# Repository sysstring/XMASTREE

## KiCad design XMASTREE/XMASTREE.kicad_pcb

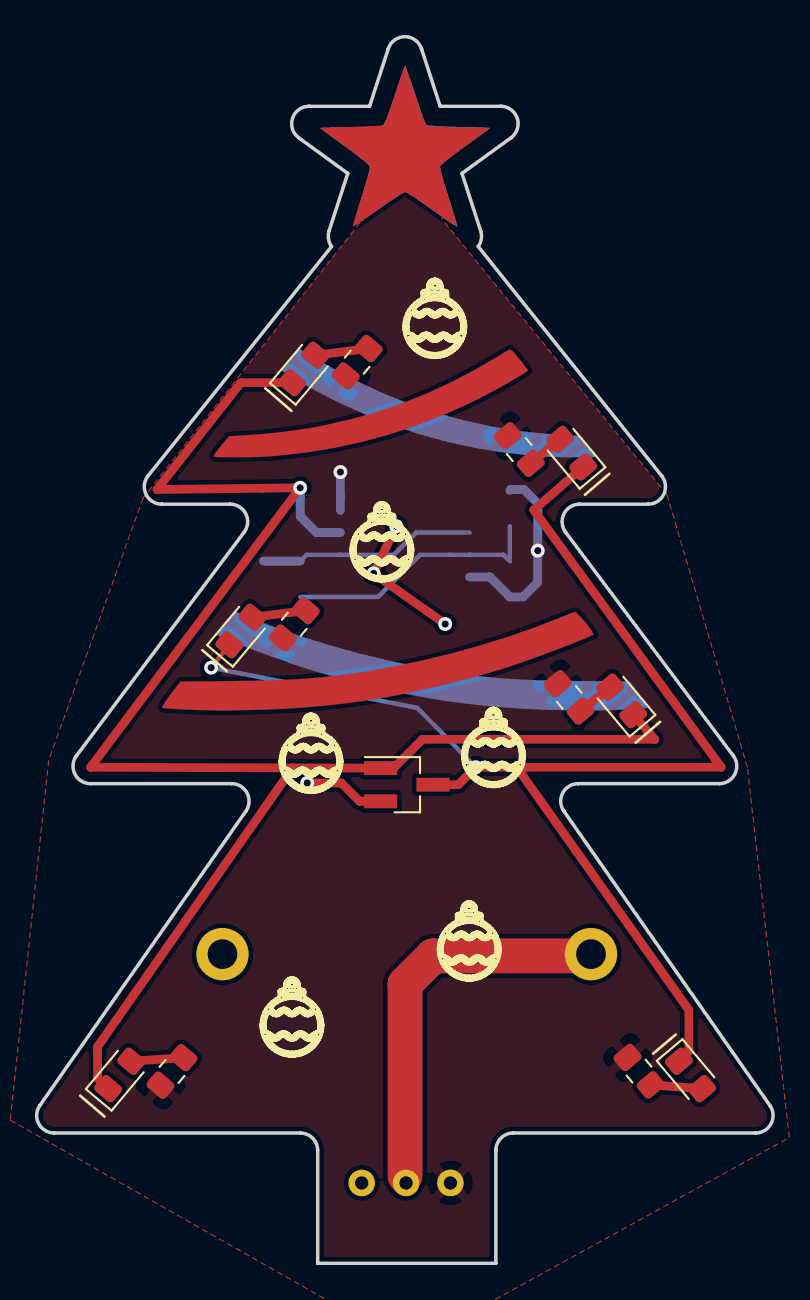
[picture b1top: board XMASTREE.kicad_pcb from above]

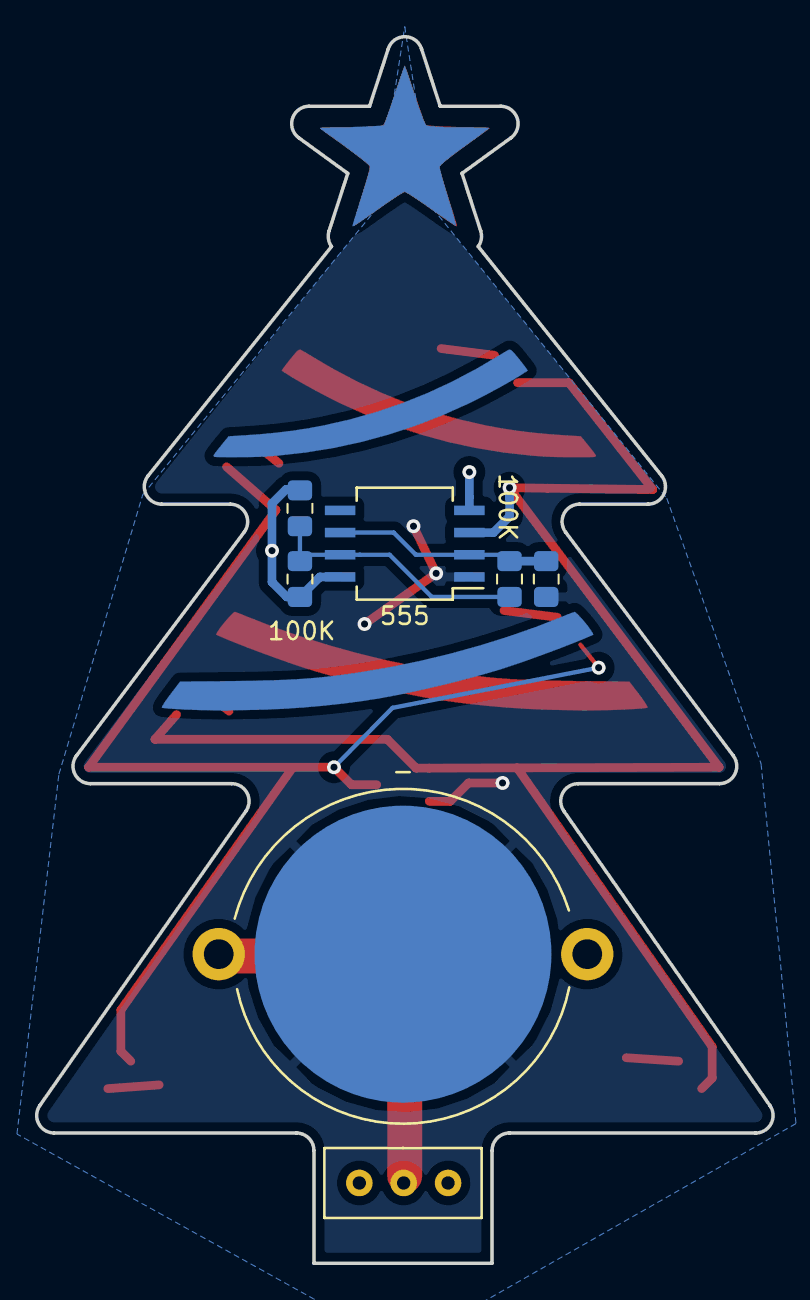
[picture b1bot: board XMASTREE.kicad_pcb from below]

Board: 2 copper layers, 42.2 x 70.2 mm, 22 parts (8 on the bottom side), 13 nets.

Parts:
100K: 100k; R_0805_2012Metric_Pad1.15x1.40mm_HandSolder
100K#2, 100K#3: 100K; R_0805_2012Metric_Pad1.15x1.40mm_HandSolder
555: TLC555; SO-8_5.3x6.2mm_P1.27mm
BT1: C2032
C1: 10u; C_0805_2012Metric_Pad1.15x1.40mm_HandSolder
D1, D2, D3, D4, D5, D6: LED; LED_0805_2012Metric_Pad1.15x1.40mm_HandSolder
Q1: Q_NMOS_GSD; SOT-23_Handsoldering
R1, R2, R4, R5, R6: 1K; R_0805_2012Metric_Pad1.15x1.40mm_HandSolder
SW1: SW_SPDT; 2.54mm_4x9mm_SPDT
TP1: Front side decoratoins; Decorations
TP2: Back side decorations; Decorations
e: 1K; R_0805_2012Metric_Pad1.15x1.40mm_HandSolder

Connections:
+BATT: 100K.1, 100K#2.2, 555.4, 555.8, R1.1, R2.1, R4.1, R5.1, R6.1, SW1.1, e.1
/BTN_COM: BT1.1, SW1.2
/INVERTED: D4.1, D5.1, D6.1, Q1.3
/OUTPUT: 555.3, D1.1, D2.1, D3.1, Q1.1
GND: 555.1, BT1.2, C1.2, Q1.2
unnamed: 100K#3.1, 555.2, 555.6, C1.1
unnamed: D1.2, R1.2
unnamed: D2.2, R2.2
unnamed: D3.2, e.2
unnamed: D4.2, R4.2
unnamed: D5.2, R5.2
unnamed: D6.2, R6.2
unnamed: 100K.2, 100K#2.1, 100K#3.2, 555.7

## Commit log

2019-10-01 schematic
2019-10-01 added battery footprint
2019-10-03 redrew schematic, prepared footprints
2019-10-03 set up board
2019-10-03 angled leds
2019-10-04 layout mostly complete
2019-10-04 added bauble file
2019-10-04 REV A
